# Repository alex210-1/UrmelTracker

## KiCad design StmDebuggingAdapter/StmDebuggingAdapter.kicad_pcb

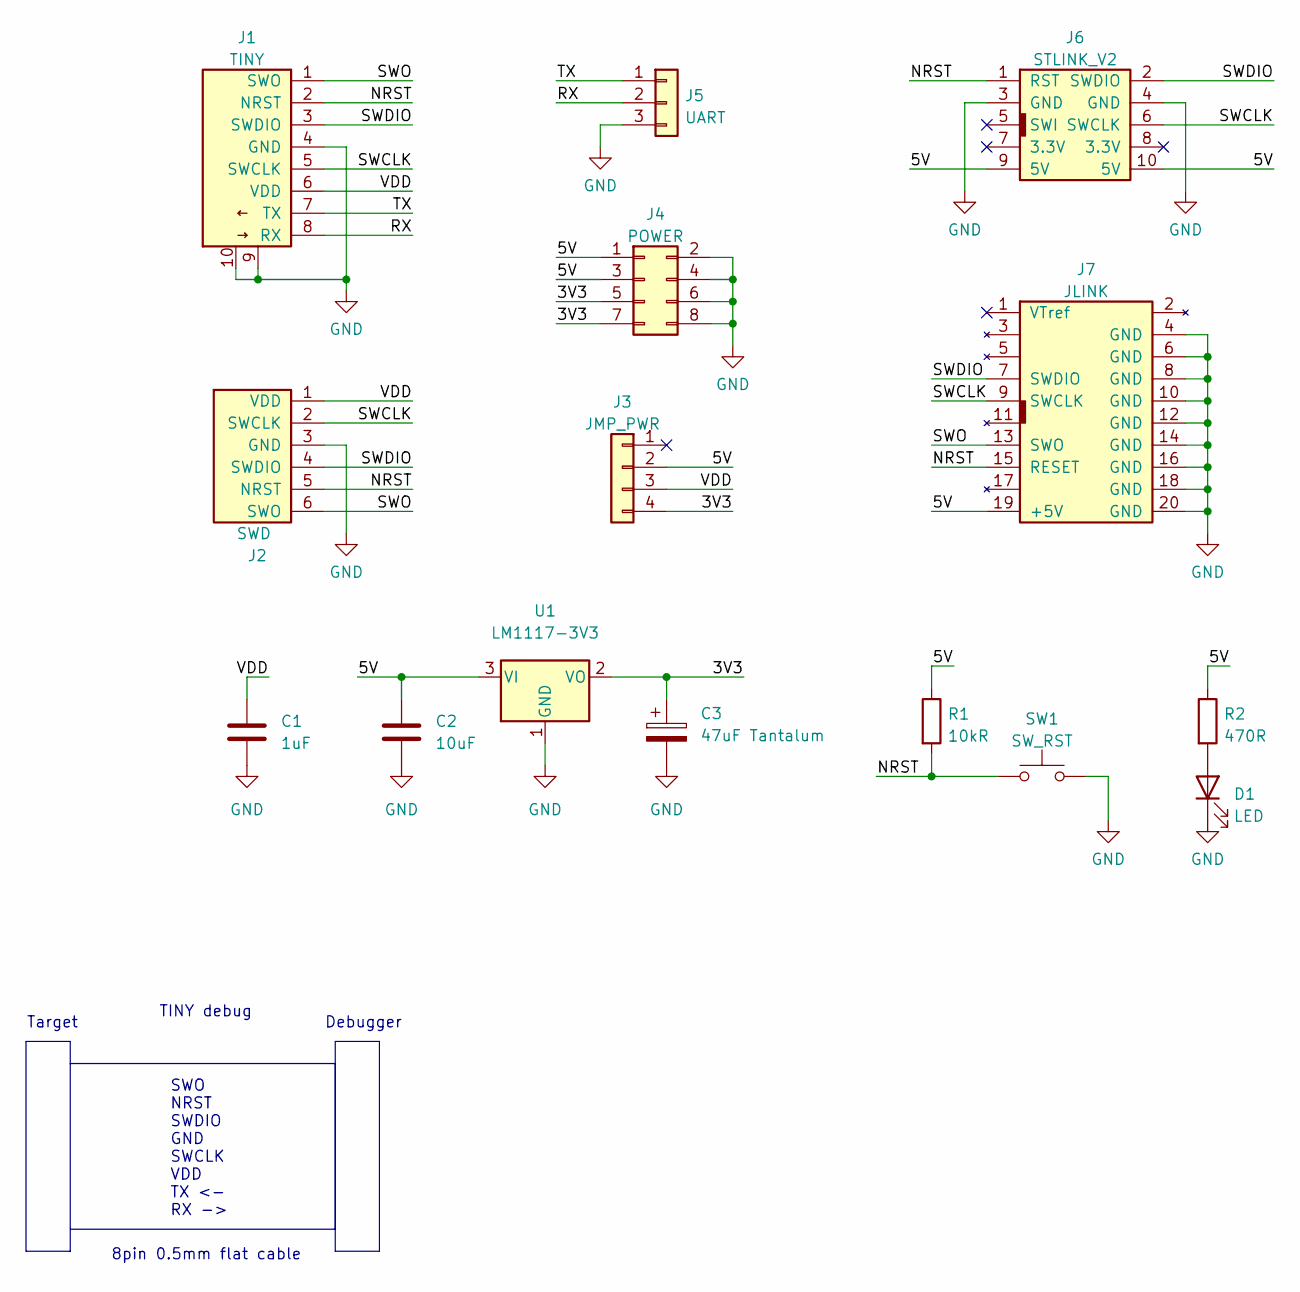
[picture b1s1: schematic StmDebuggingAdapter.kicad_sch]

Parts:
C1: 1uF; C_0805_2012Metric_Pad1.18x1.45mm_HandSolder
C2: 10uF; C_0805_2012Metric_Pad1.18x1.45mm_HandSolder
C3: 47uF Tantalum; CP_EIA-6032-28_Kemet-C_Pad2.25x2.35mm_HandSolder
D1: LED; LED_0603_1608Metric_Pad1.05x0.95mm_HandSolder
J1: TINY; Hirose_FH12-8S-0.5SH_1x08-1MP_P0.50mm_Horizontal
J2: SWD; PinHeader_1x06_P2.54mm_Vertical
J3: JMP_PWR; PinHeader_1x04_P2.54mm_Vertical
J4: POWER; PinHeader_2x04_P2.54mm_Vertical
J5: UART; PinHeader_1x03_P2.54mm_Vertical
J6: STLINK_V2; IDC-Header_2x05_P2.54mm_Vertical
J7: JLINK; IDC-Header_2x10_P2.54mm_Vertical
R1: 10kR; R_0805_2012Metric_Pad1.20x1.40mm_HandSolder
R2: 470R; R_0805_2012Metric_Pad1.20x1.40mm_HandSolder
SW1: SW_RST; SW_Push_1P1T_NO_6x6mm_H9.5mm
U1: LM1117-3V3; SOT-223-3_TabPin2

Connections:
/3V3: C3.1, J3.4, J4.5, J4.7, U1.2 (VO)
/5V: C2.1, J3.2, J4.1, J4.3, J6.9 (5V), J6.10 (5V), J7.19 (+5V), R1.1, R2.1, U1.3 (VI)
/NRST: J1.2 (NRST), J2.5 (NRST), J6.1 (RST), J7.15 (RESET), R1.2, SW1.1
/RX: J1.8 (RX), J5.2
/SWCLK: J1.5 (SWCLK), J2.2 (SWCLK), J6.6 (SWCLK), J7.9 (SWCLK)
/SWDIO: J1.3 (SWDIO), J2.4 (SWDIO), J6.2 (SWDIO), J7.7 (SWDIO)
/SWO: J1.1 (SWO), J2.6 (SWO), J7.13 (SWO)
/TX: J1.7 (TX), J5.1
/VDD: C1.1, J1.6 (VDD), J2.1 (VDD), J3.3
GND: C1.2, C2.2, C3.2, D1.1 (K), J1.4 (GND), J1.9, J1.10, J2.3 (GND), J4.2, J4.4, J4.6, J4.8, J5.3, J6.3 (GND), J6.4 (GND), J7.4 (GND), J7.6 (GND), J7.8 (GND), J7.10 (GND), J7.12 (GND), J7.14 (GND), J7.16 (GND), J7.18 (GND), J7.20 (GND), SW1.2, U1.1 (GND); also elsewhere on the board
unnamed 10: D1.2 (A), R2.2; also elsewhere on the board

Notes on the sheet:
8pin 0.5mm flat cable
Debugger
SWO NRST SWDIO GND SWCLK VDD TX <- RX ->
Target
TINY debug

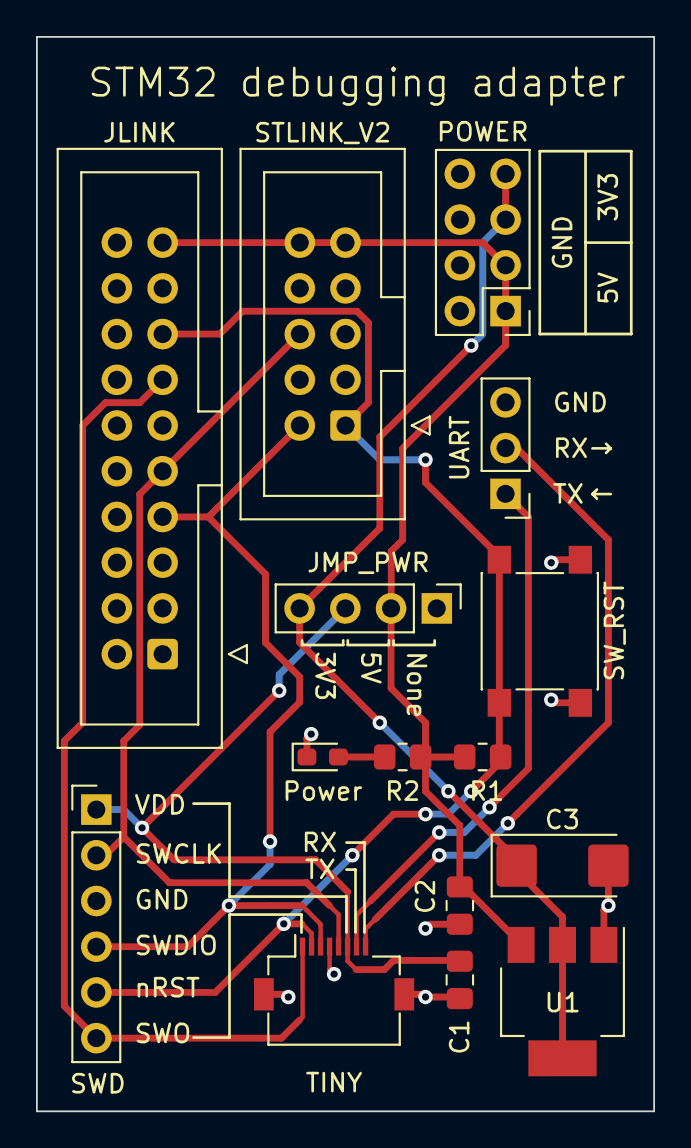
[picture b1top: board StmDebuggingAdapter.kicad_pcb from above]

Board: 2 copper layers, 34.3 x 59.7 mm, 15 parts (0 on the bottom side), 11 nets.

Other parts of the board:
Power: LED; LED_0603_1608Metric_Pad1.05x0.95mm_HandSolder

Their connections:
GND: Power.1 (K); also elsewhere on the board
unnamed 10: Power.2 (A); also elsewhere on the board

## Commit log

2022-10-15 initial, docs
2022-10-15 stmDebuggerPcb
